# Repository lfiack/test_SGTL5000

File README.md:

# Test SGTL5000
Test board for the SGTL5000 CODEC

## Notes
* SAI1_FS_A stands for frame synchronization, might be connected to CODEC's I2S_LRCLK pin (32/48/96kHz)
* SAI1_SD_A stands for serial data, connect to CODEC's I2S_DIN pin
* SAI1_SD_B is SAI B Synchronous Slave's serial data, connect to I2S_DOUT
* SAI1_SCK_A connect to I2S_SCLK (32/64 times FS frequency)
* SAI1_MCLK_A connecto to SYS_MCLK
    * "An integrated PLL is provided in the SGTL5000 that allows any clock from 8.0 to 27 MHz to be connected to SYS_MCLK"

* CODEC's CTRL_CLK is I2C SCL
* CODEC's CTRL_DATA is I2C SDA

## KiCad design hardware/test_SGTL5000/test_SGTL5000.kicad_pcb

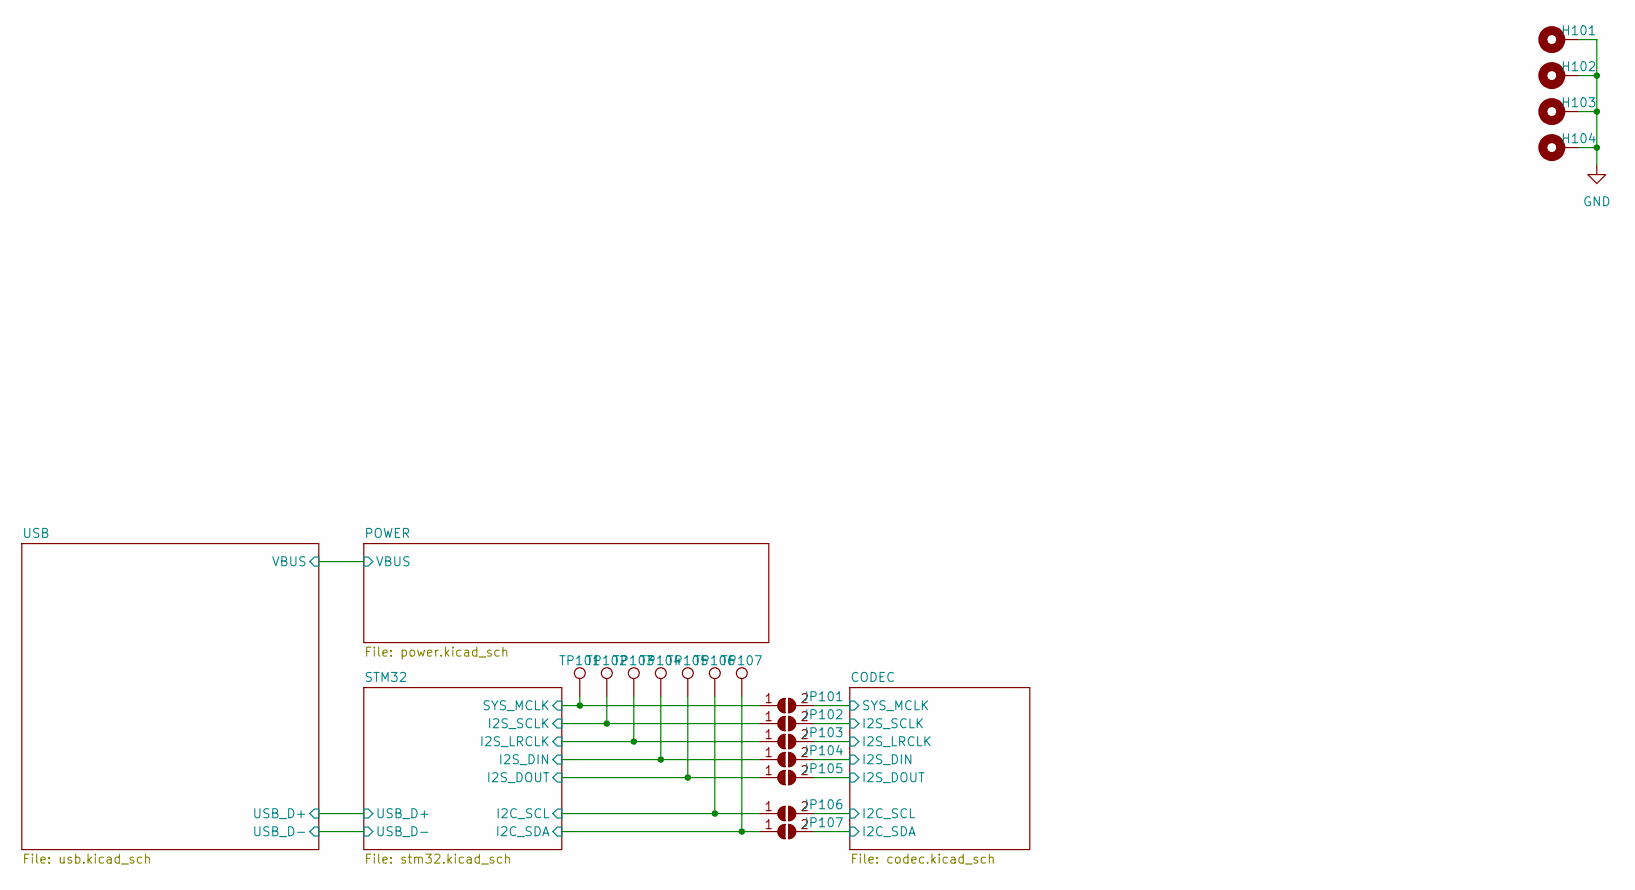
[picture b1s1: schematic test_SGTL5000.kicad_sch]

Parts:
H101, H102, H103, H104: MountingHole_Pad; MountingHole_3.2mm_M3_Pad_Via
JP101, JP102, JP103, JP104, JP105, JP106, JP107: SolderJumper_2_Open; R_0603_1608Metric
TP101, TP102, TP103, TP104, TP105, TP106, TP107: TestPoint; TestPoint_Pad_D1.5mm

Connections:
/CODEC/I2C_SCL: JP106.2 (B); also elsewhere on the board
/CODEC/I2C_SDA: JP107.2 (B); also elsewhere on the board
/CODEC/I2S_DIN: JP104.2 (B); also elsewhere on the board
/CODEC/I2S_DOUT: JP105.2 (B); also elsewhere on the board
/CODEC/I2S_LRCLK: JP103.2 (B); also elsewhere on the board
/CODEC/I2S_SCLK: JP102.2 (B); also elsewhere on the board
/CODEC/SYS_MCLK: JP101.2 (B); also elsewhere on the board
/STM32/I2C_SCL: JP106.1 (A), TP106.1; also elsewhere on the board
/STM32/I2C_SDA: JP107.1 (A), TP107.1; also elsewhere on the board
/STM32/I2S_DIN: JP104.1 (A), TP104.1; also elsewhere on the board
/STM32/I2S_DOUT: JP105.1 (A), TP105.1; also elsewhere on the board
/STM32/I2S_LRCLK: JP103.1 (A), TP103.1; also elsewhere on the board
/STM32/I2S_SCLK: JP102.1 (A), TP102.1; also elsewhere on the board
/STM32/SYS_MCLK: JP101.1 (A), TP101.1; also elsewhere on the board
GND: H101.1, H102.1, H103.1, H104.1; also elsewhere on the board

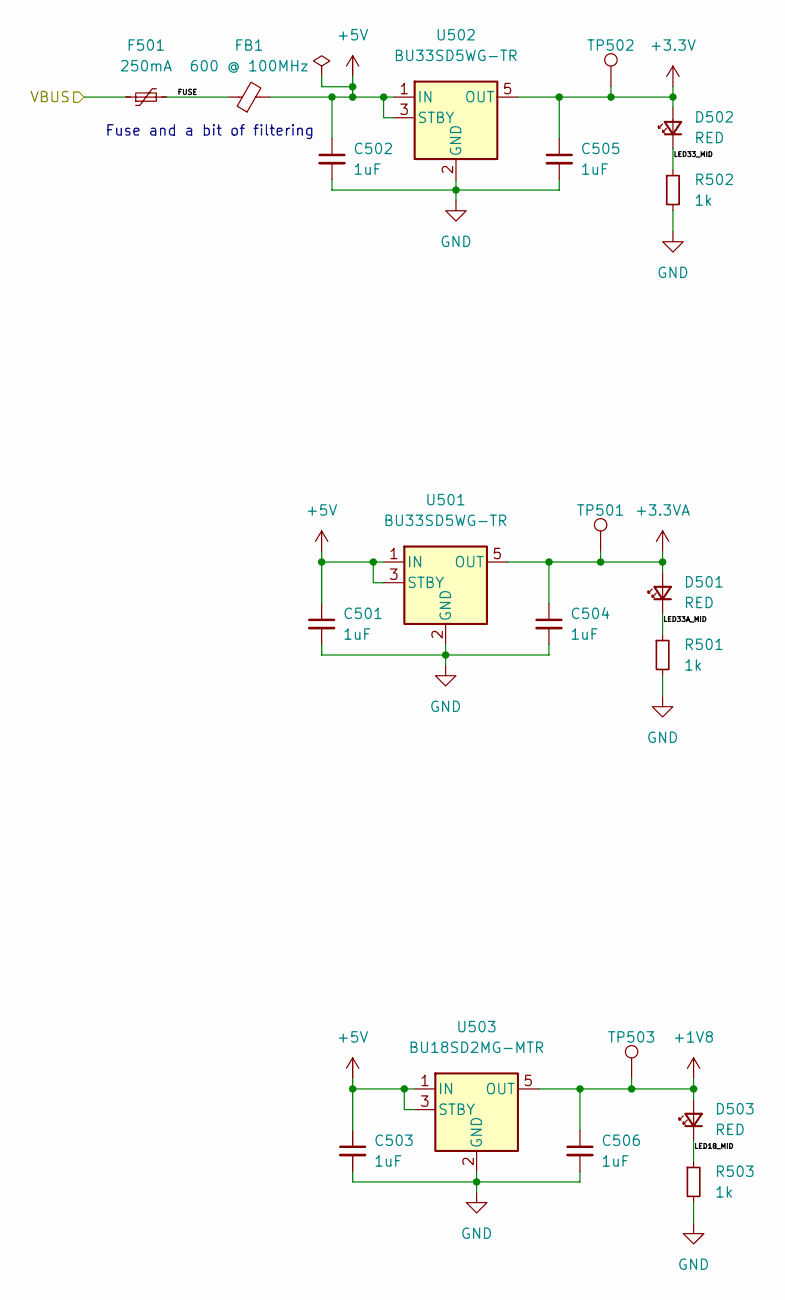
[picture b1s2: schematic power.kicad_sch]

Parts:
C501, C502, C503, C504, C505, C506: 1uF; C_0603_1608Metric
D501, D502, D503: RED; LED_0603_1608Metric
F501: 250mA; Fuse_1206_3216Metric; Farnell 2834880
FB1: 600 @ 100MHz; L_0805_2012Metric_Pad1.15x1.40mm_HandSolder; Farnell 2292460
R501, R502, R503: 1k; R_0603_1608Metric
TP501, TP502, TP503: TestPoint; TestPoint_Pad_D1.5mm
U501, U502: BU33SD5WG-TR; SOT-23-5
U503: BU18SD2MG-MTR; SOT-23-5

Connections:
+1V8: C506.1, D503.2 (A), TP503.1, U503.5 (OUT); also elsewhere on the board
+3.3VA: C504.1, D501.2 (A), TP501.1, U501.5 (OUT); also elsewhere on the board
+3V3: C505.1, D502.2 (A), TP502.1, U502.5 (OUT); also elsewhere on the board
+5V: C501.1, C502.1, C503.1, FB1.2, U501.1 (IN), U501.3 (STBY), U502.1 (IN), U502.3 (STBY), U503.1 (IN), U503.3 (STBY)
/POWER/FUSE: F501.2, FB1.1
/POWER/LED18_MID: D503.1 (K), R503.1
/POWER/LED33A_MID: D501.1 (K), R501.1
/POWER/LED33_MID: D502.1 (K), R502.1
/POWER/VBUS: F501.1; also elsewhere on the board
GND: C501.2, C502.2, C503.2, C504.2, C505.2, C506.2, R501.2, R502.2, R503.2, U501.2 (GND), U502.2 (GND), U503.2 (GND); also elsewhere on the board

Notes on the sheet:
Fuse and a bit of filtering

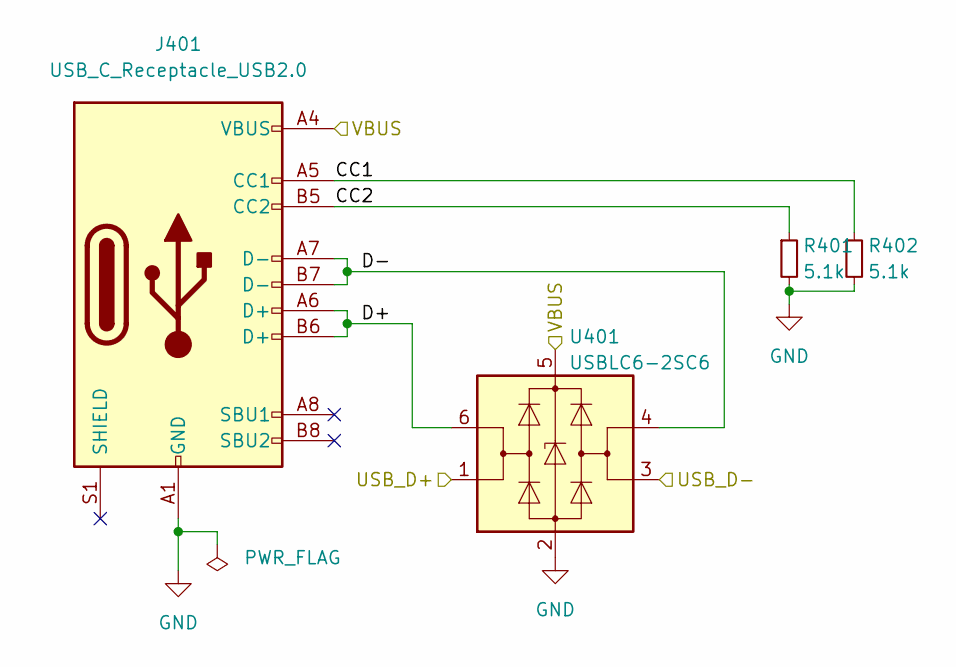
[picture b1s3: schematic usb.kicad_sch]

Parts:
J401: USB_C_Receptacle_USB2.0; USB_C_Receptacle_HRO_TYPE-C-31-M-12
R401, R402: 5.1k; R_0603_1608Metric
U401: USBLC6-2SC6; SOT-23-6

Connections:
/POWER/VBUS: J401.A4 (VBUS), J401.A9 (VBUS), J401.B4 (VBUS), J401.B9 (VBUS), U401.5 (VBUS); also elsewhere on the board
/STM32/USB_D+: U401.1 (I/O1); also elsewhere on the board
/STM32/USB_D-: U401.3 (I/O2); also elsewhere on the board
/USB/CC1: J401.A5 (CC1), R402.1
/USB/CC2: J401.B5 (CC2), R401.1
/USB/D+: J401.A6 (D+), J401.B6 (D+), U401.6 (I/O1)
/USB/D-: J401.A7 (D-), J401.B7 (D-), U401.4 (I/O2)
GND: J401.A1 (GND), J401.A12 (GND), J401.B1 (GND), J401.B12 (GND), R401.2, R402.2, U401.2 (GND); also elsewhere on the board

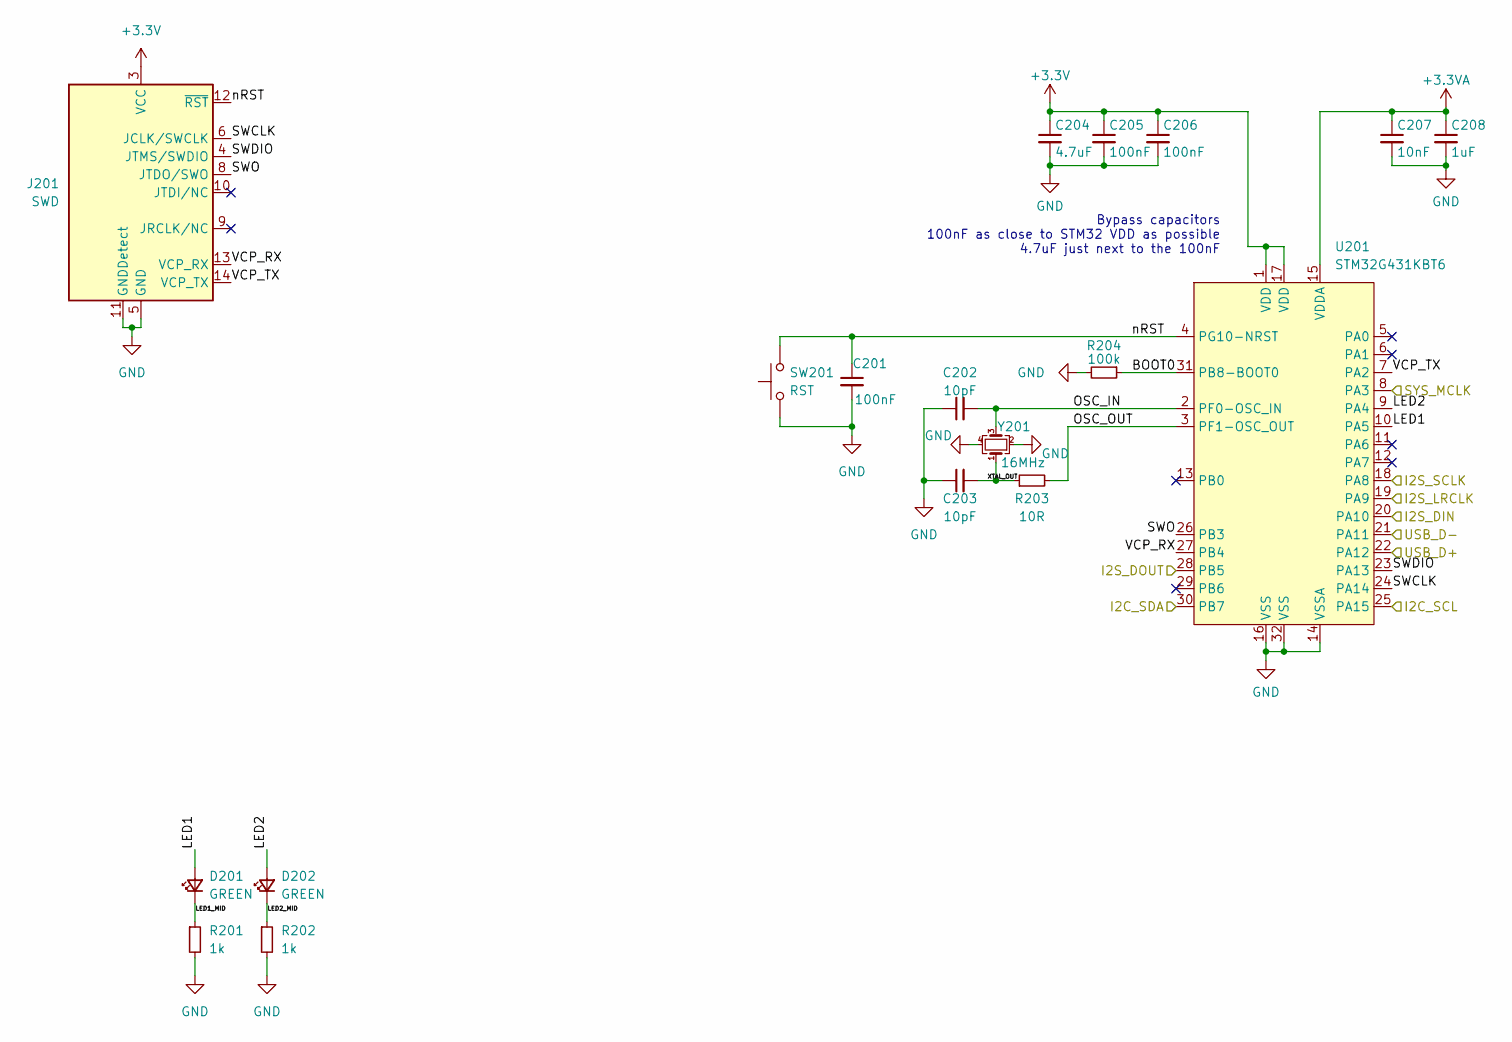
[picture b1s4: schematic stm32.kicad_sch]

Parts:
C201, C205, C206: 100nF; C_0402_1005Metric
C202, C203: 10pF; C_0402_1005Metric
C204: 4.7uF; C_0603_1608Metric; Farnell 3013398
C207: 10nF; C_0402_1005Metric
C208: 1uF; C_0603_1608Metric; Farnell 3013398
D201, D202: GREEN; LED_0603_1608Metric
J201: SWD; PinHeader_2x07_P1.27mm_Vertical_SMD
R201, R202: 1k; R_0603_1608Metric
R203: 10R; R_0603_1608Metric
R204: 100k; R_0402_1005Metric
SW201: RST; SW_SPST_B3U-1000P; Farnell 1333652
U201: STM32G431KBT6; LQFP-32_7x7mm_P0.8mm
Y201: 16MHz; Crystal_SMD_EuroQuartz_MT-4Pin_3.2x2.5mm; Farnell 2853935

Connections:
+3.3VA: C207.1, C208.1, U201.15 (VDDA); also elsewhere on the board
+3V3: C204.1, C205.1, C206.1, J201.3 (VCC), U201.1 (VDD), U201.17 (VDD); also elsewhere on the board
/STM32/BOOT0: R204.1, U201.31 (PB8-BOOT0)
/STM32/I2C_SCL: U201.25 (PA15); also elsewhere on the board
/STM32/I2C_SDA: U201.30 (PB7); also elsewhere on the board
/STM32/I2S_DIN: U201.20 (PA10); also elsewhere on the board
/STM32/I2S_DOUT: U201.28 (PB5); also elsewhere on the board
/STM32/I2S_LRCLK: U201.19 (PA9); also elsewhere on the board
/STM32/I2S_SCLK: U201.18 (PA8); also elsewhere on the board
/STM32/LED1: D201.2 (A), U201.10 (PA5)
/STM32/LED1_MID: D201.1 (K), R201.1
/STM32/LED2: D202.2 (A), U201.9 (PA4)
/STM32/LED2_MID: D202.1 (K), R202.1
/STM32/OSC_IN: C202.2, U201.2 (PF0-OSC_IN), Y201.3
/STM32/OSC_OUT: R203.2, U201.3 (PF1-OSC_OUT)
/STM32/SWCLK: J201.6 (JCLK/SWCLK), U201.24 (PA14)
/STM32/SWDIO: J201.4 (JTMS/SWDIO), U201.23 (PA13)
/STM32/SWO: J201.8 (JTDO/SWO), U201.26 (PB3)
/STM32/SYS_MCLK: U201.8 (PA3); also elsewhere on the board
/STM32/USB_D+: U201.22 (PA12); also elsewhere on the board
/STM32/USB_D-: U201.21 (PA11); also elsewhere on the board
/STM32/VCP_RX: J201.13 (VCP_RX), U201.27 (PB4)
/STM32/VCP_TX: J201.14 (VCP_TX), U201.7 (PA2)
/STM32/XTAL_OUT: C203.2, R203.1, Y201.1
/STM32/nRST: C201.1, J201.12 (~RST), SW201.2, U201.4 (PG10-NRST)
GND: C201.2, C202.1, C203.1, C204.2, C205.2, C206.2, C207.2, C208.2, J201.5 (GND), J201.7 (GND), J201.11 (GNDDetect), R201.2, R202.2, R204.2, SW201.1, U201.14 (VSSA), U201.16 (VSS), U201.32 (VSS), Y201.2, Y201.4; also elsewhere on the board

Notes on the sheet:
Bypass capacitors 100nF as close to STM32 VDD as possible 4.7uF just next to the 100nF

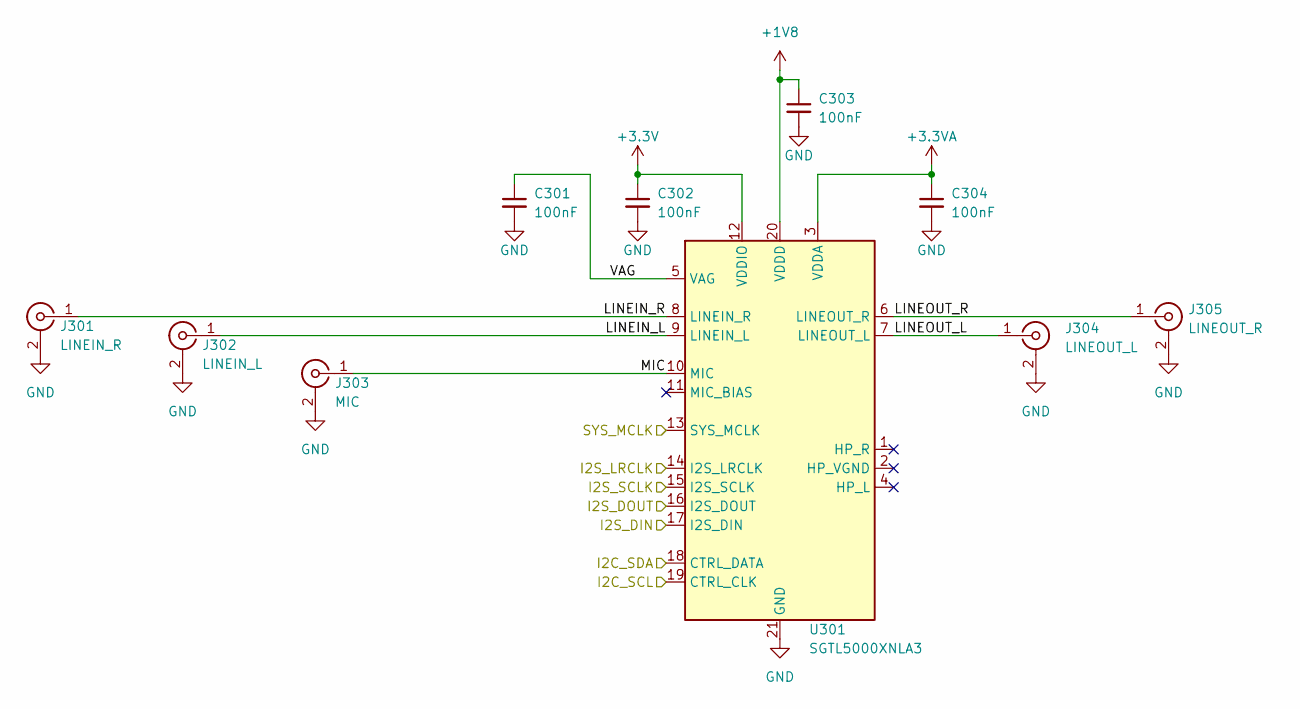
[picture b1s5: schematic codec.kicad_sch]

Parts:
C301, C302, C303, C304: 100nF; C_0402_1005Metric
J301: LINEIN_R; BNC_RS-PRO_546-4027
J302: LINEIN_L; BNC_RS-PRO_546-4027
J303: MIC; BNC_RS-PRO_546-4027
J304: LINEOUT_L; BNC_RS-PRO_546-4027
J305: LINEOUT_R; BNC_RS-PRO_546-4027
U301: SGTL5000XNLA3; QFN-20-1EP_3x3mm_P0.4mm_EP1.65x1.65mm

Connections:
+1V8: C303.1, U301.20 (VDDD); also elsewhere on the board
+3.3VA: C304.1, U301.3 (VDDA); also elsewhere on the board
+3V3: C302.1, U301.12 (VDDIO); also elsewhere on the board
/CODEC/I2C_SCL: U301.19 (CTRL_CLK); also elsewhere on the board
/CODEC/I2C_SDA: U301.18 (CTRL_DATA); also elsewhere on the board
/CODEC/I2S_DIN: U301.17 (I2S_DIN); also elsewhere on the board
/CODEC/I2S_DOUT: U301.16 (I2S_DOUT); also elsewhere on the board
/CODEC/I2S_LRCLK: U301.14 (I2S_LRCLK); also elsewhere on the board
/CODEC/I2S_SCLK: U301.15 (I2S_SCLK); also elsewhere on the board
/CODEC/LINEIN_L: J302.1 (In), U301.9 (LINEIN_L)
/CODEC/LINEIN_R: J301.1 (In), U301.8 (LINEIN_R)
/CODEC/LINEOUT_L: J304.1 (In), U301.7 (LINEOUT_L)
/CODEC/LINEOUT_R: J305.1 (In), U301.6 (LINEOUT_R)
/CODEC/MIC: J303.1 (In), U301.10 (MIC)
/CODEC/SYS_MCLK: U301.13 (SYS_MCLK); also elsewhere on the board
/CODEC/VAG: C301.1, U301.5 (VAG)
GND: C301.2, C302.2, C303.2, C304.2, J301.2 (Ext), J302.2 (Ext), J303.2 (Ext), J304.2 (Ext), J305.2 (Ext), U301.21 (GND); also elsewhere on the board

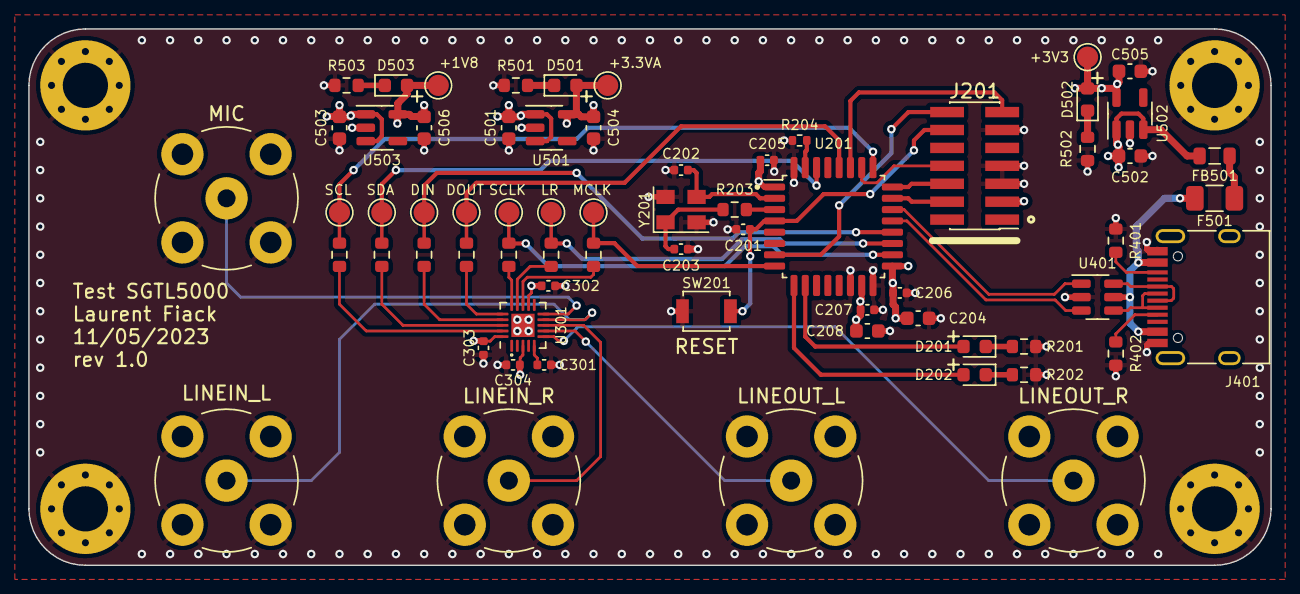
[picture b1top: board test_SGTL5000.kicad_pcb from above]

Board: 4 copper layers, 88.0 x 38.0 mm, 70 parts (0 on the bottom side), 50 nets.

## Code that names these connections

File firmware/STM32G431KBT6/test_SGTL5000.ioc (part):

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Mcu.Name=STM32G431K(6-8-B)Tx
Mcu.Package=LQFP32
Mcu.UserName=STM32G431KBTx
PA10.Mode=SAI_A_MasterWithClock
PA10.Signal=SAI1_SD_A
PA11.Mode=Device
PA11.Signal=USB_DM
PA12.Mode=Device
PA12.Signal=USB_DP
PA13.Mode=Trace_Asynchronous_SW
PA13.Signal=SYS_JTMS-SWDIO
PA14.Mode=Trace_Asynchronous_SW
PA14.Signal=SYS_JTCK-SWCLK
PA15.Mode=I2C
PA15.Signal=I2C1_SCL
PA2.Mode=Asynchronous
PA2.Signal=USART2_TX
PA3.Mode=SAI_A_MasterWithClock
PA3.Signal=SAI1_MCLK_A
PA4.GPIOParameters=GPIO_Label
PA4.GPIO_Label=LED2
PA4.Signal=GPIO_Output
PA5.GPIOParameters=GPIO_Label
PA5.GPIO_Label=LED1
PA5.Signal=GPIO_Output
PA8.Mode=SAI_A_MasterWithClock
PA8.Signal=SAI1_SCK_A
PA9.Mode=SAI_A_MasterWithClock
PA9.Signal=SAI1_FS_A
PB3.Mode=Trace_Asynchronous_SW
PB3.Signal=SYS_JTDO-SWO
PB4.Mode=Asynchronous
PB4.Signal=USART2_RX
PB5.Mode=SAI_B_SyncSlave
PB5.Signal=SAI1_SD_B
PB7.Mode=I2C
PB7.Signal=I2C1_SDA
PF0-OSC_IN.Mode=HSE-External-Oscillator
PF0-OSC_IN.Signal=RCC_OSC_IN
PF1-OSC_OUT.Mode=HSE-External-Oscillator
PF1-OSC_OUT.Signal=RCC_OSC_OUT
RCC.HSE_VALUE=16000000
RCC.SYSCLKFreq_VALUE=170000000
RCC.SYSCLKSource=RCC_SYSCLKSOURCE_PLLCLK
board=custom

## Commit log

2023-03-21 tests with ioc
2023-03-23 kicad project
2023-04-04 schema
2023-04-19 routing
2023-04-20 Started routing
2023-05-11 finished routing
2023-05-11 small mod
2023-05-30 fabrication files
